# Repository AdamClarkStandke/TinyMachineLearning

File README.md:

# TinyMachineLearning

Developing Embedded Applications that for the most part deal with machine learning as detailed from the following books and tutorials:

- [TinyML Cookbook by Gian Iodice](https://www.packtpub.com/product/tinyml-cookbook/9781801814973)
- [Teach an Arduino to Fly by David McGriffy](https://www.makershed.com/products/make-drones-pdf)

As Gian details Tiny machine learning is broadly defined as a fast growing field of machine learning technologies and applications including hardware (dedicated integrated circuits), algorithms and software capable of performing on-device sensor (vision, audio, IMU, biomedical, etc.) data analytics at extremely low power, typically in the mW range and below, and hence enabling a variety of always-on use-cases and targeting battery operated devices.[^1]

This Branch contains the most updated code and hardware designs. The branch old_documentation contains older code/designs and applications that do not fit with the main repo. 

## MicroController Boards

**Arduino Nano 33 BLE Sense Rev2**

| | Description |
| --- | --- |
| CPU | Arm Cortex-M4 64MHz |
| FLASH | 1MB |
| RAM | 256KB |
| SIZE | 45x18mm |

As bought and documented [here](https://store-usa.arduino.cc/products/nano-33-ble-sense-rev2?selectedStore=us)

**Rasperry Pi Pico W RP2040 MicroController**

| | Description |
| --- | --- |
| CPU | Dual core Arm Cortex-M0+ 133MHz |
| FLASH | 2MB |
| RAM | 264KB |
|Wifi| 2.4GHz single band, 802.11n 
| SIZE | 51x21mm |

As bought and documented [here](https://www.adafruit.com/product/5526)

## Project: Gesture Sense Emmoji Keyboard

Implementation of [Get Started With Machine Learning on Arduino](https://docs.arduino.cc/tutorials/nano-33-ble-sense-rev2/get-started-with-machine-learning#capturing-gesture-training-data) by Sandeep Mistry and Dominic Pajak. A gesture classifier is created to play Street Fighter as detailed by Charlie Gerard in [Play Street Fighter with body movements using Arduino and Tensorflow.js](https://medium.com/@devdevcharlie/play-street-fighter-with-body-movements-using-arduino-and-tensorflow-js-6b0e4734e118). Full implementation can be found [here](https://github.com/arduino/AIoT-Dev-Summit-2019)

### Getting Gesture Data with BMI270 and BMM150 Sensors

The x-axis represents the num of samples and the y-axis represents g-force from the accelerometer and degrees per second from the gyroscope. 

**Jab Data**

Acceleration Graph:

Angular velocity Graph:

Raw data can be found [here](https://github.com/AdamClarkStandke/TinyMachineLearning/blob/main/punch.csv)

**Upper Cut Data**

Acceleration Graph:

Angular velocity Graph:

Raw data can be found [here](https://github.com/AdamClarkStandke/TinyMachineLearning/blob/main/upper_cut.csv)

### Training and Validation Learning Curves 

The learning curves after 300 epochs of training mixed with validation as seen below:

with the following model and trainable paramaters:

| Layer (type)| Output Shape| Param #|
| ------------- | ------------- |--------|
| Dense | 50| 35,750|
| Dense | 15| 765|
| Dense | 2| 32|

Ino Code can be found [here](https://github.com/AdamClarkStandke/TinyMachineLearning/blob/main/gestureDetection_classifier/gestureDetection_classifier.ino)

C-Byte Model can be found [here](https://github.com/AdamClarkStandke/TinyMachineLearning/blob/main/gestureDetection_classifier/model.h)

## Project: Person Detection with Rasperry Pi Pico W

Implementation of the person detection example as detailed by the [ArduCam Team](https://github.com/ArduCAM/RPI-Pico-Cam)

[.jpg)](https://www.youtube.com/watch?v=MaYkYJmJrqk)

## Project: Drone Flight Control System using the Arduino Nano 33 BLE Sense Rev2 Board 

WARNING!!! THIS PROJECT IS AN OPEN SOURCE HARDWARE PROJECT TAKE ALL PRECATIONS BEFORE ASSEMBLY SUCH AS MASK, GLOVES AND FIRE EXTINGUISHER. IN THAT REGARD READ THE [MIT LICENSE](https://github.com/AdamClarkStandke/TinyMachineLearning/blob/main/LICENSE) ALSO  BEFORE USING!!!!

### Schematic and PCB layout:

This version of the schematic comes from the book [Teach an Arduino to Fly by David McGriffy](https://www.makershed.com/products/make-drones-pdf) in the book David uses the [Teensy 3.1](https://www.pjrc.com/teensy/teensy31.html) board and the add-in for the Arduino IDE to program the flight controller, I just switched the board and removed the  components that are not necessary for the Nano BLE 33 Rev 2. This design uses only one 3.7V 650mAh battery rather then the two that I used in the previous two designs. This should help with the weight issues I was having. To make this design work you need to buy a voltage regulator/booster (similar to the one I designed in Old Version 1) except in this design I bought a tried and tested booster (rather than design my own like I did in Old Version 1); in particular I bought [Matek VB2A5V 3-4.2V to 5V Voltage Booster ](https://www.racedayquads.com/products/matek-vb2a5-1s-lipo-to-5v-voltage-booster?currency=USD&variant=31467728207985&gclid=Cj0KCQjw0IGnBhDUARIsAMwFDLnRW7vPnVI_kPZZ07VLbTDB3pQNJlU3sNtUL8EGRetb_AuOmo7wnHUaAl3fEALw_wcB). Basically, the genius of David's design is that a 3.7v battery can be used to power the Arduino, motors, and other components. The battery's 3.7-4.2 variable discharge rate will power the motors, while the regulated 5v output  will power the Arduino through its vin pin and the auxiliary components (i.e a camera). The Arduino's 3v3 pin is configured to power the [Lemon RX reciever](https://lemon-rx.com/index.php?route=product/product&product_id=263) to be controlled by the [Blade MLP4DSM 4Ch Controller](https://www.horizonhobby.com/product/mlp4dsm-4ch-transmitter-2.4ghz-bmcx2120s/EFLH1064B.html?gclid=Cj0KCQjw0IGnBhDUARIsAMwFDLnIMOxdLQWNxmZvSB9TNVZfrrQnBrdQ40ycnGwFcJZ92rF96O86bkgaAlpqEALw_wcB). However, I first need to understand how the Serial 1 hardware library works with the Nano (which to one of ordinary skill will take some additional time); so to save time, I will be building a joystick control system as detailed by [paulsb](https://www.hackster.io/paulsb/drone-joystick-controller-25e036) through the Nano's Bluetooth BLE. And I decided to add a FPV camera manufactured by [Wolfwhoop](https://www.amazon.com/Wolfwhoop-Adjustable-Transmitter-Cloverleaf-Aircraft/dp/B06XB2ZRBP/ref=pd_bxgy_sccl_1/132-0789857-4412803?pd_rd_w=KdcOt&content-id=amzn1.sym.43d28dfc-aa4f-4ef6-b591-5ab7095e137f&pf_rd_p=43d28dfc-aa4f-4ef6-b591-5ab7095e137f&pf_rd_r=0ZG0660FKA7GD9XJE3BV&pd_rd_wg=1bQHZ&pd_rd_r=90a10e5a-f0e7-4b4d-99c3-937c4bba083c&pd_rd_i=B06XB2ZRBP&psc=1) to capture video images.The drone frame is a [Syma X5C Frame](https://www.amazon.com/Syma-Channel-2-4GHz-Explorers-Copter/dp/B00MNG37C2/ref=asc_df_B00MNG37C2/?tag=hyprod-20&linkCode=df0&hvadid=312184153387&hvpos=&hvnetw=g&hvrand=2952487919274782735&hvpone=&hvptwo=&hvqmt=&hvdev=c&hvdvcmdl=&hvlocint=&hvlocphy=9006587&hvtargid=pla-587640326317&psc=1) and I modified David's code as found at [The visible drone](http://www.makedronesbook.com/projects/VizDrone) to work for the Nano 33 BLE 33 Rev2 and Nano 33 BLE. Get David's book to fully understand this Drone/flight control game, G!!! (highly recommended). 

**Schematic**

**Gerber file and 3D Gerber CAD VIEW**

PCB Fabrication and assembly was done by [EasyEda](https://easyeda.com/).

[Gerber File](https://github.com/AdamClarkStandke/TinyMachineLearning/blob/main/Gerber_PCB_PCB_ArudinoDrone_2023-08-19_2023-08-20.zip)

### Generic Flight Control System:

[Drone Flight Control System](https://github.com/AdamClarkStandke/TinyMachineLearning/tree/main/DCS)

[JoyStick Controller](https://github.com/AdamClarkStandke/TinyMachineLearning/blob/main/contorl_test_ble/contorl_test_ble.ino)

### AI Flight Control System:

<!--Because the drone frames available in [learning to fly](https://github.com/utiasDSL/gym-pybullet-drones/tree/master/gym_pybullet_drones/assets) are different from the drone frame that I will be using I needed to model the drone frame [//]:  (as best I could) in [blender](https://www.blender.org/). That way it could be simulated kind of accurately in the [learning to fly](https://github.com/utiasDSL/gym-pybullet-drones/tree/master/) rl environmnet. I used the [cf2.dae](https://github.com/utiasDSL/gym-pybullet-drones/blob/master/gym_pybullet_drones/assets/cf2.dae) as a template in regards to modeling the propellers:   

[//]:  [Custom Drone](https://github.com/AdamClarkStandke/TinyMachineLearning/blob/main/customDrone.dae)

[//]:  I then created a [urdf file](http://wiki.ros.org/urdf) to import the collada file I created in blender and used the defualt properties, joints, and links found in the other drone frames in learning to fly.  

[//]:  [RoboCain](https://github.com/AdamClarkStandke/TinyMachineLearning/blob/main/droneOne.urdf)

[//]:  And the drone frame was able to be simulated in the [learning to fly](https://github.com/utiasDSL/gym-pybullet-drones/tree/master/) rl environment as seen below in the fly.py example:

[//]:  -->

-------------------------------------------------------------------------------
## Reference:
[^1]: [TinyML](https://www.tinyml.org/about/)
[^2]: Need to also get the get [ArduCam OV2640 MINI 2MP-Plus header file](https://github.com/ArduCAM/Arduino); choose the right camera module in the memorysaver.h; and download the JPEG library for things to work

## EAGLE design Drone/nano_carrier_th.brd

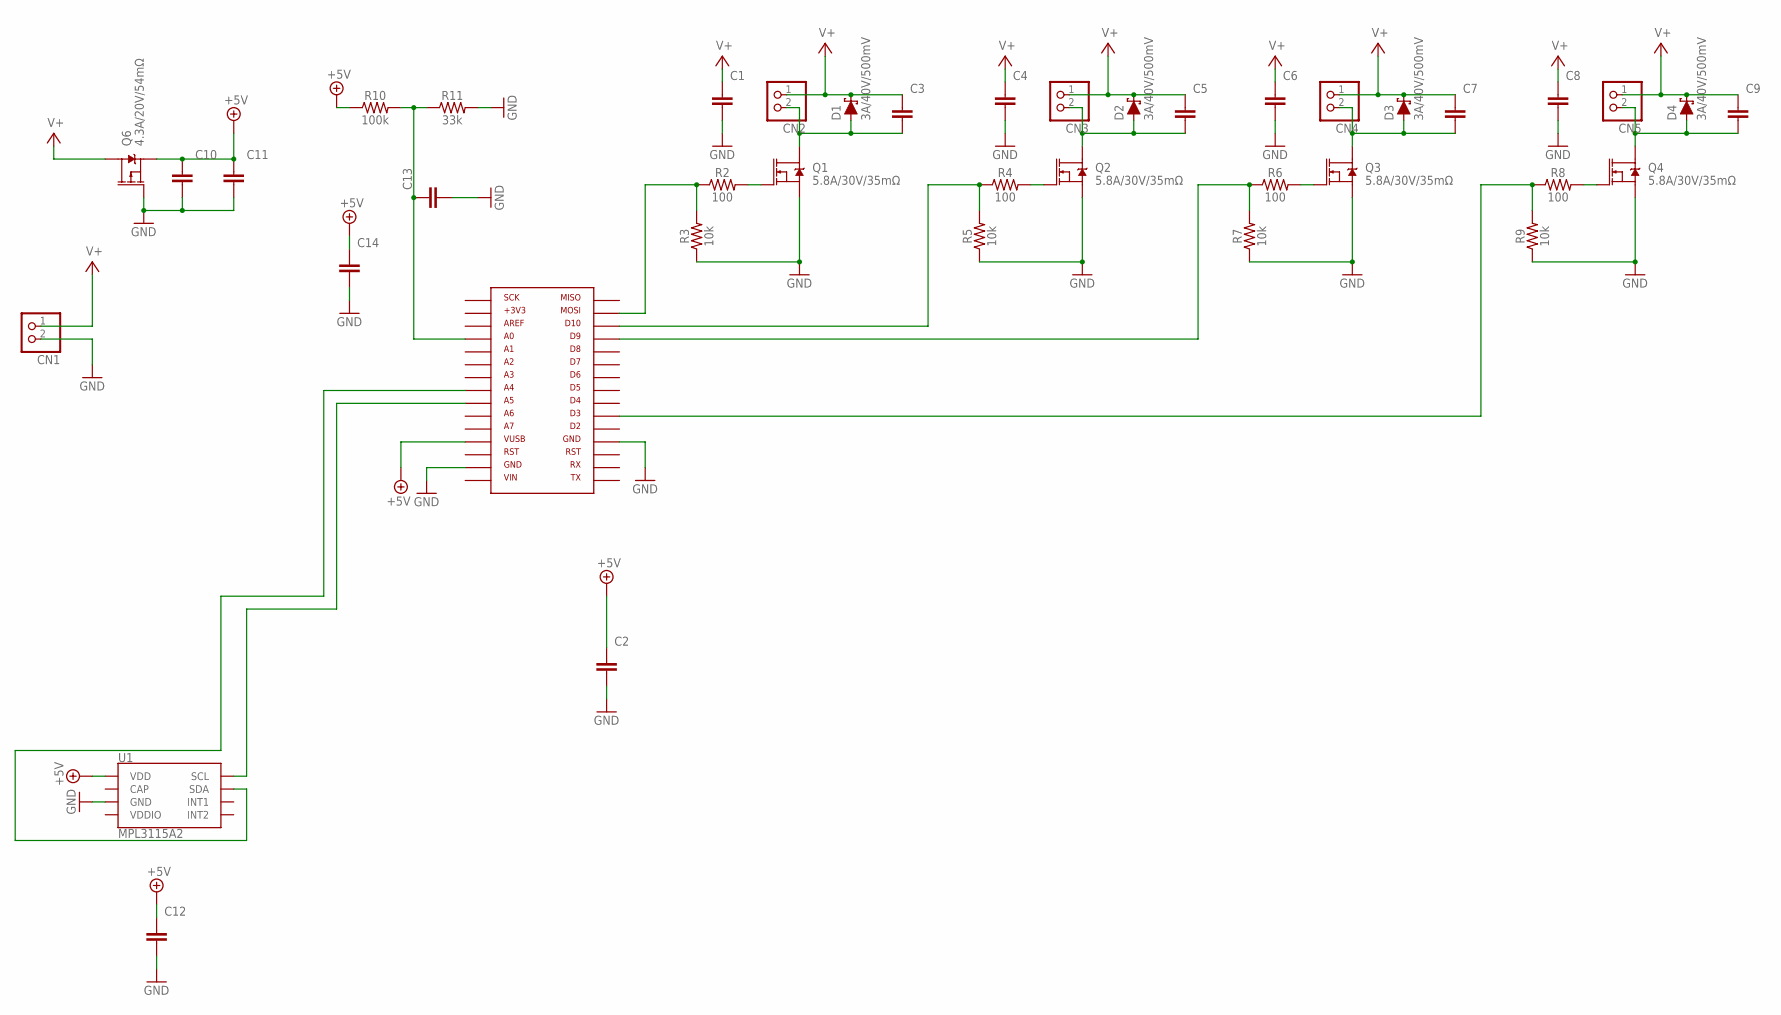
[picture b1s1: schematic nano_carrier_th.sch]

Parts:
C1, C4, C6, C8, C12, C13, C14: 22uF; CAPM3216X180
C2: 10uF; CAPM3216X180
C3, C5, C7, C9: 10nF; CAPM3216X180
C10, C11: C_TANTALUM-1206(3216-METRIC); CAPM3216X180
CN1, CN2, CN3, CN4, CN5: JST_2PIN-THM; JST-PH-2-THM
D1, D2, D3, D4: 3A/40V/500mV; SMA-DIODE
Q1, Q2, Q3, Q4: 5.8A/30V/35mΩ; SOT23-3
Q6: 4.3A/20V/54mΩ; SOT23-3
R2, R4, R6, R8: 100; 0603
R3, R5, R7, R9: 10k; 0603
R10: 100k; 0603
R11: 33k; 0603
U1: MPL3115A2; LGA-8-5X3
U$1: NANO-TH

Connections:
+5V: C2.1, C10.1, C11.1, C12.1, C14.1, Q6.2 (S), R10.1, U1.1 (VDD), U$1.P$12
CAP: U1.2 (CAP)
GND: C1.2, C2.2, C4.2, C6.2, C8.2, C10.2, C11.2, C12.2, C13.2, C14.2, CN1.2 (1), Q1.2 (S), Q2.2 (S), Q3.2 (S), Q4.2 (S), Q6.1 (G), R3.1, R5.1, R7.1, R9.1, R11.2, U1.3 (GND), U$1.P$14, U$1.P$19
unnamed: R2.1, R3.2, U$1.P$29
unnamed: Q1.1 (G), R2.2
unnamed: C3.2, CN2.2 (1), D1.A, Q1.3 (D)
unnamed: R4.1, R5.2, U$1.P$28
unnamed: Q2.1 (G), R4.2
unnamed: C5.2, CN3.2 (1), D2.A, Q2.3 (D)
unnamed: R6.1, R7.2, U$1.P$27
unnamed: Q3.1 (G), R6.2
unnamed: C7.2, CN4.2 (1), D3.A, Q3.3 (D)
unnamed: R8.1, R9.2, U$1.P$21
unnamed: Q4.1 (G), R8.2
unnamed: C9.2, CN5.2 (1), D4.A, Q4.3 (D)
unnamed: U1.8 (SCL), U$1.P$9
unnamed: U1.7 (SDA), U$1.P$8
unnamed: C13.1, R10.2, R11.1, U$1.P$4
V+: C1.1, C3.1, C4.1, C5.1, C6.1, C7.1, C8.1, C9.1, CN1.1 (2), CN2.1 (2), CN3.1 (2), CN4.1 (2), CN5.1 (2), D1.C, D2.C, D3.C, D4.C, Q6.3 (D)
VDDIO: U1.4 (VDDIO)

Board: 2 copper layers, 40 parts (0 on the bottom side), 18 nets, no tracks yet.

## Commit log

2023-03-13 Created using Colaboratory
2023-06-03 Add files via upload
    initial drone control code
2023-06-04 Add files via upload
    Drone Motor Control over BLE communication
2023-06-16 openAI/pybullet reinforcement learning for quadcopter
2023-10-15 Add files via upload
    Added the basic framework for the Drone Control System
2023-10-16 Add files via upload
    Working with the MaahonyAHRS filter to not get wrong values for roll, pitch, and yaw
2023-10-19 Add files via upload
    fixed reading of IMU values sent to Mahony filter; working on debugging Joystick Controller
2023-10-20 Add files via upload
    Implemented dual joystick controller for the BLE communication for the rcvalues of throttle,roll, pitch, and yaw
2023-10-20 Add files via upload
    makeshift dual joystick controller made out of a rat trap lol for now
2023-10-22 Add files via upload
    Started PID tuning, set default values of 0.5 for all controller values for P parameter of BLE controller; have not touched I or D

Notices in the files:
parts and their libraries:
SparkFun-Resistors: Licensing: Creative Commons ShareAlike 4.0 International - https://creativecommons.org/licenses/by-sa/4.0
